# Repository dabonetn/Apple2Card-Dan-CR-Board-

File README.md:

This is my take on a surface mount version of the DAN II Card.

This version removes all the debug headers, and adds jumpers to the resistors for the Wiznet Header. (R27 & R28 on the original board)

ICSP port always provides power, and I don't recommend adding a header to this connector, but just use a male pinheader to program the unit.

This schematic allows cutting a jumper for 27256 or 27512 eprom chips programmed at the beginning of the chip, or leave it as is and program these chips at offset $4000.

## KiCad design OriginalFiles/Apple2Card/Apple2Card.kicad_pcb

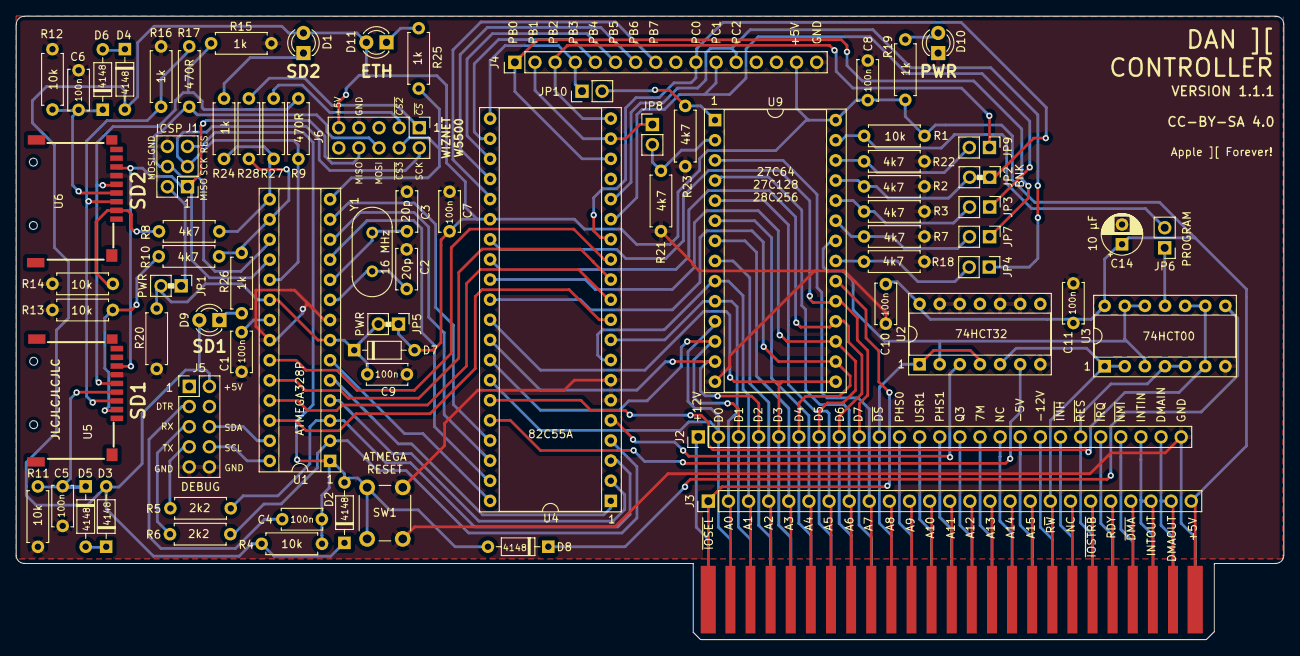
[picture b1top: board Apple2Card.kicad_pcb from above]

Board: 2 copper layers, 160.0 x 78.7 mm, 77 parts (0 on the bottom side), 116 nets.

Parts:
BUS1: Apple2Bus; Apple2Slot
C1, C4, C5, C6, C7, C8, C9, C10, C11: 100n; C_Disc_D5.0mm_W2.5mm_P5.00mm
C2, C3: 20p; C_Disc_D5.0mm_W2.5mm_P5.00mm
C14: 10 µF; CP_Radial_D5.0mm_P2.50mm
D1, D9, D10, D11: LED; LED_D3.0mm
D2, D3, D4, D5, D6, D7, D8: 4148; D_DO-35_SOD27_P7.62mm_Horizontal
J1: ICSP; PinHeader_2x03_P2.54mm_Vertical
J2, J3: Conn_01x25; PinHeader_1x25_P2.54mm_Vertical
J4: Conn_01x16; PinHeader_1x16_P2.54mm_Vertical
J5: SERCON; PinHeader_2x05_P2.54mm_Vertical
J6: WIZNET 5500; PinHeader_2x05_P2.54mm_Vertical
JP1, JP5: PWR; PinHeader_1x02_P2.54mm_Vertical
JP2: PG0; PinHeader_1x02_P2.54mm_Vertical
JP3: PG1; PinHeader_1x02_P2.54mm_Vertical
JP4, JP9: PG2; PinHeader_1x02_P2.54mm_Vertical
JP6: PROGRAM; PinHeader_1x02_P2.54mm_Vertical
JP7: PG3; PinHeader_1x02_P2.54mm_Vertical
JP8: PG4; PinHeader_1x02_P2.54mm_Vertical
JP10: PG9; PinHeader_1x02_P2.54mm_Vertical
R1, R4, R11, R12, R13, R14, R20: 10k; R_Axial_DIN0207_L6.3mm_D2.5mm_P7.62mm_Horizontal
R2, R3, R7, R8, R10, R18, R21, R22, R23: 4k7; R_Axial_DIN0207_L6.3mm_D2.5mm_P7.62mm_Horizontal
R5, R6: 2k2; R_Axial_DIN0207_L6.3mm_D2.5mm_P7.62mm_Horizontal
R9, R17, R27, R28: 470R; R_Axial_DIN0207_L6.3mm_D2.5mm_P7.62mm_Horizontal
R15, R16, R19, R24, R25, R26: 1k; R_Axial_DIN0207_L6.3mm_D2.5mm_P7.62mm_Horizontal
SW1: SW_Push; SW_PUSH_6mm
U1: ATmega328P-P; DIP-28_W7.62mm_Socket
U2: 74HCT32; DIP-14_W7.62mm_Socket
U3: 74HCT00; DIP-14_W7.62mm_Socket
U4: 82C55A; DIP-40_W15.24mm_Socket
U5: Slot1; GCT-MEM2055-00-190-01-A
U6: Slot2; GCT-MEM2055-00-190-01-A
U9: 28C256; DIP-28_W15.24mm_Socket
Y1: 16 MHz; Crystal_HC49-U_Vertical

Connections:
+5V: BUS1.25 (+5V), C7.1, C8.1, C10.1, C11.1, C14.1, D1.2 (A), D2.1 (K), D3.2 (A), D4.2 (A), D7.2 (A), D9.2 (A), D11.2 (A), J3.25, J4.15, J5.2, J6.9, JP5.1 (A), R1.1, R4.1, R19.1, U2.14 (VCC), U3.14 (VCC), U4.26 (VCC), U9.28 (VCC)
A0: BUS1.2 (A0), J3.2, U4.9 (A0), U9.10 (A0)
A1: BUS1.3 (A1), J3.3, U4.8 (A1), U9.9 (A1)
A2: BUS1.4 (A2), J3.4, U9.8 (A2)
A3: BUS1.5 (A3), J3.5, U9.7 (A3)
A4: BUS1.6 (A4), J3.6, U9.6 (A4)
A5: BUS1.7 (A5), J3.7, U9.5 (A5)
A6: BUS1.8 (A6), J3.8, U9.4 (A6)
A7: BUS1.9 (A7), J3.9, U9.3 (A7)
ACKA: U1.25 (PC2), U4.11 (PC6)
CS: R10.1, R26.2, R28.1, U1.16 (PB2)
CS2: R8.1, R24.2, R27.1, U1.15 (PB1)
CS3: J6.4, R25.2, U1.14 (PB0)
D0: BUS1.49 (D0), J2.2, U4.34 (D0), U9.11 (D0)
D1: BUS1.48 (D1), J2.3, U4.33 (D1), U9.12 (D1)
D2: BUS1.47 (D2), J2.4, U4.32 (D2), U9.13 (D2)
D3: BUS1.46 (D3), J2.5, U4.31 (D3), U9.15 (D3)
D4: BUS1.45 (D4), J2.6, U4.30 (D4), U9.16 (D4)
D5: BUS1.44 (D5), J2.7, U4.29 (D5), U9.17 (D5)
D6: BUS1.43 (D6), J2.8, U4.28 (D6), U9.18 (D6)
D7: BUS1.42 (D7), J2.9, U4.27 (D7), U9.19 (D7)
DS: BUS1.41 (~DEVICE_SELECT), J2.10, U2.1, U2.4
GND: BUS1.26 (GND), C1.2, C2.2, C3.2, C5.2, C6.2, C7.2, C8.2, C9.2, C10.2, C11.2, C14.2, D10.1 (K), J1.6, J2.25, J4.16, J5.9, J5.10, J6.7, R2.2, R3.2, R7.2, R11.1, R12.1, R13.2, R14.2, R15.2, R16.2, R18.2, R20.1, R21.2, R22.2, R23.2, SW1.2, U1.8 (GND), U1.22 (GND), U2.7 (GND), U2.9, U2.10, U2.12, U2.13, U3.7 (GND), U4.6 (~CS), U4.7 (GND), U5.6 (GND), U6.6 (GND), U9.14 (GND)
IBFA: U1.24 (PC1), U4.12 (PC5)
IOSEL: BUS1.1 (~IOSEL), J3.1, U9.20 (~CS)
MISO: J1.1, J6.8, U1.18 (PB4), U5.7 (DO), U6.7 (DO)
MOSI: J1.4, J6.6, R17.2, U1.17 (PB3)
unnamed: BUS1.10 (A8), J3.10
unnamed: BUS1.11 (A9), J3.11
unnamed: BUS1.12 (A10), J3.12
unnamed: BUS1.13 (A11), J3.13
unnamed: BUS1.14 (A12), J3.14
unnamed: BUS1.15 (A13), J3.15
unnamed: BUS1.16 (A14), J3.16
unnamed: BUS1.17 (A15), J3.17
unnamed: BUS1.19 (NC), J3.19
unnamed: BUS1.20 (~IO_STROBE), J3.20
unnamed: BUS1.21 (RDY), J3.21
unnamed: BUS1.22 (~DMA), J3.22
unnamed: BUS1.23 (INT_OUT), BUS1.28 (INT_IN), J2.23, J3.23
unnamed: BUS1.24 (DMA_OUT), BUS1.27 (DMA_IN), J2.24, J3.24
unnamed: BUS1.29 (~NMI), J2.22
unnamed: BUS1.30 (~IRQ), J2.21
unnamed: BUS1.32 (~INH), J2.19
unnamed: BUS1.33 (-12V), J2.18
unnamed: BUS1.34 (-5V), J2.17
unnamed: BUS1.35 (NC), J2.16
unnamed: BUS1.36 (7M), J2.15
unnamed: BUS1.37 (Q3), J2.14
unnamed: BUS1.38 (PHASE1), J2.13
unnamed: BUS1.39 (USER_1), J2.12
unnamed: BUS1.40 (PHASE0), J2.11
unnamed: BUS1.50 (+12V), J2.1
unnamed: C1.1, U1.21 (AREF)
unnamed: C2.1, U1.9 (XTAL1/PB6), Y1.2
unnamed: C3.1, U1.10 (XTAL2/PB7), Y1.1
unnamed: C4.1, J5.3
unnamed: C5.1, D5.1 (K), R11.2, U5.4 (VDD)
unnamed: C6.1, D6.1 (K), R12.2, U6.4 (VDD)
unnamed: C9.1, D7.1 (K), JP1.2 (B), JP5.2 (B), R20.2, U1.7 (VCC), U1.20 (AVCC)
unnamed: D1.1 (K), R24.1
unnamed: D3.1 (K), D5.2 (A)
unnamed: D4.1 (K), D6.2 (A)
unnamed: D8.1 (K), U3.8
unnamed: D9.1 (K), R26.1
unnamed: D10.2 (A), R19.2
unnamed: D11.1 (K), R25.1
unnamed: J1.2, JP1.1 (A)
unnamed: J4.5, U4.22 (PB4)
unnamed: J4.6, U4.23 (PB5)
unnamed: J4.7, U4.24 (PB6)
unnamed: J4.8, U4.25 (PB7)
unnamed: J5.5, R6.1
unnamed: J5.7, R5.1
unnamed: J6.1, R28.2
unnamed: J6.3, R27.2
unnamed: JP2.2 (B), R2.1, U9.25 (A8)
unnamed: JP3.2 (B), R3.1, U9.24 (A9)
unnamed: JP4.2 (B), R18.1, U9.21 (A10)
unnamed: JP6.1 (A), U3.11
unnamed: JP6.2 (B), R1.2, U9.27 (~WE)
unnamed: JP7.2 (B), R7.1, U9.23 (A11)
unnamed: JP8.2 (B), R21.1, U9.2 (A12)
unnamed: JP9.2 (B), R22.1, U9.26 (A13)
unnamed: JP10.2 (B), R23.1, U9.1 (A14)
unnamed: R10.2, R13.1, U5.2 (~CS)
unnamed: R8.2, R14.1, U6.2 (~CS)
unnamed: R9.2, R15.1, U5.5 (SCLK), U6.5 (SCLK)
unnamed: R16.1, R17.1, U5.3 (DI), U6.3 (DI)
unnamed: U2.2, U3.3, U3.12, U3.13, U9.22 (~OE)
unnamed: U2.3, U4.5 (~RD)
unnamed: U2.6, U4.36 (~WR)
unnamed: U3.6, U3.9, U3.10, U4.35 (RESET)
OBFA: U1.26 (PC3), U4.10 (PC7)
PB0: J4.1, JP7.1 (A), U4.18 (PB0)
PB1: J4.2, JP8.1 (A), U4.19 (PB1)
PB2: J4.3, JP9.1 (A), U4.20 (PB2)
PB3: J4.4, JP10.1 (A), U4.21 (PB3)
PC0: J4.10, JP2.1 (A), U4.14 (PC0)
PC1: J4.11, JP3.1 (A), U4.15 (PC1)
PC2: J4.12, JP4.1 (A), U4.16 (PC2)
PC4: J5.6, U1.27 (PC4)
PC5: J5.8, U1.28 (PC5)
PD0: R6.2, U1.2 (PD0), U4.4 (PA0)
PD1: R5.2, U1.3 (PD1), U4.3 (PA1)
PD2: U1.4 (PD2), U4.2 (PA2)
PD3: U1.5 (PD3), U4.1 (PA3)
PD4: U1.6 (PD4), U4.40 (PA4)
PD5: U1.11 (PD5), U4.39 (PA5)
PD6: U1.12 (PD6), U4.38 (PA6)
PD7: U1.13 (PD7), U4.37 (PA7)
RES: BUS1.31 (~RES), J2.20, U3.4, U3.5
RESET: C4.2, D2.2 (A), D8.2 (A), J1.5, R4.2, SW1.1, U1.1 (~RESET/PC6)
RW: BUS1.18 (R/~W), J3.18, U2.5, U3.1, U3.2
SCK: J1.3, J6.2, R9.1, U1.19 (PB5)
STBA: U1.23 (PC0), U4.13 (PC4)

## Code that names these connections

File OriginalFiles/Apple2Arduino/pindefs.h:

/* pindefs.h */
/* by Daniel L. Marks */

/*
 * Copyright (c) 2022 Daniel Marks

This software is provided 'as-is', without any express or implied
warranty. In no event will the authors be held liable for any damages
arising from the use of this software.

Permission is granted to anyone to use this software for any purpose,
including commercial applications, and to alter it and redistribute it
freely, subject to the following restrictions:

1. The origin of this software must not be misrepresented; you must not
   claim that you wrote the original software. If you use this software
   in a product, an acknowledgment in the product documentation would be
   appreciated but is not required.
2. Altered source versions must be plainly marked as such, and must not be
   misrepresented as being the original software.
3. This notice may not be removed or altered from any source distribution.
 */

#ifndef _PINDEFS_H
#define _PINDEFS_H

#define DAN_328P  3
#define DAN_644P  4

#if defined(__AVR_ATmega328P__)
#define CS     2    // PB2
#define CS2    1     // PB1
#define CS3    0     // PB0
#define D_CS3  8     // PB0 in Arduino Digital pin

#define MOSI   3    // PB3
#define MISO   4    // PB4
#define SCK    5    // PB5

#define STBA   0  // PC0
#define IBFA   1  // PC1
#define ACKA   2  // PC2
#define OBFA   3  // PC3
#define DAN_CARD     DAN_328P
#elif defined(__AVR_ATmega644P__)
#define CS     2     // PB2
#define CS2    1     // PB1
#define CS3    0     // PB0
#define D_CS3  8     // PB0 in Arduino Digital pin

#define MOSI   5    // PB5
#define MISO   6    // PB6
#define SCK    7    // PB7
#define SLAVE_S 4   // PB4 SS PIN *needs* to be configured as it's floating!

#define STBA   6  // PC6
#define IBFA   7  // PC7
#define ACKA   2  // PC2
#define OBFA   3  // PC3
#define DAN_CARD     DAN_644P
#else
#error Invalid platform for pindef.h!
#endif

#define SOFTWARE_SERIAL
#define SOFTWARE_SERIAL_RX A4
#define SOFTWARE_SERIAL_TX A5

#define CS_ALL			(_BV(CS)|_BV(CS2)|_BV(CS3))
/* Make sure we never use PORTB = XXX as it nukes settings for the SS pin */
#define DISABLE_CS() do { PORTB |= CS_ALL; DDRB |= CS_ALL; } while (0)
#define DISABLE_RXTX_PINS() UCSR0B &= ~(_BV(RXEN0)|_BV(TXEN0)|_BV(RXCIE0)|_BV(UDRIE0))
#define ENABLE_RXTX_PINS() UCSR0B |= (_BV(RXEN0)|_BV(TXEN0)|_BV(RXCIE0)|_BV(UDRIE0))
#define WAIT_TX() while ((UCSR0A & _BV(TXC0) == 0)

#define DATAPORT_MODE_TRANS() DDRD = 0xFF
#define DATAPORT_MODE_RECEIVE() do { PORTD = 0x00; DDRD = 0x00; } while (0)

#define READ_DATAPORT() (PIND)
#define WRITE_DATAPORT(x) do { uint8_t temp = (x); PORTD=temp; PORTD=temp; } while (0)

#define READ_OBFA() (PINC & _BV(OBFA))
#define READ_IBFA() (PINC & _BV(IBFA))
#define ACK_LOW_SINGLE() PORTC &= ~_BV(ACKA)
#define ACK_HIGH_SINGLE() PORTC |= _BV(ACKA)
#define STB_LOW_SINGLE() PORTC &= ~_BV(STBA)
#define STB_HIGH_SINGLE() PORTC |= _BV(STBA)

/* Needed to slow down data send for 82C55 */

// Ack has to be 200ns -- 16mhz AVR cycle is ~63
// ACK to data available is 175ns, so 3 cycles of ACK low should be enough
#define ACK_LOW() do { \
                     ACK_LOW_SINGLE(); ACK_LOW_SINGLE(); ACK_LOW_SINGLE(); \
                     ACK_LOW_SINGLE(); ACK_LOW_SINGLE(); \
                  } while (0)
// the read operation should be one cycle, so we reach 200ns and we can release ACK immediately
#define ACK_HIGH() do { ACK_HIGH_SINGLE();  } while (0)
// STB to IBS is 150ns, that's 3 AVR cycles, however, we don't /need/ to wait, we could just read IBS
#define STB_LOW() do { \
                        STB_LOW_SINGLE(); STB_LOW_SINGLE(); STB_LOW_SINGLE(); \
                        STB_LOW_SINGLE(); STB_LOW_SINGLE();\
                  } while (0)
#define STB_HIGH() do { STB_HIGH_SINGLE(); } while (0)

#define INITIALIZE_CONTROL_PORT() do { \
  PORTC |= (_BV(STBA) | _BV(IBFA) | _BV(ACKA) | _BV(OBFA)); \
  DDRC |= (_BV(STBA) | _BV(ACKA)); \
  DDRC &= ~(_BV(IBFA) | _BV(OBFA)); \
  PORTC |= (_BV(STBA) | _BV(IBFA) | _BV(ACKA) | _BV(OBFA)); \
} while (0)

#endif /* _PINDEFS_H */

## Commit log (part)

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2023-03-18 Improved boot menu. Added title and footer bar. Added ":" separators. Added option to keep existing card selection by pressing RETURN. Wipe screen before reboot. Swapped RETURN and SPACE keys in ROM 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
2023-03-24 Improved SD-card compatibility (and performance)
    1. Compatibility fix for some SD cards
    After a power-down an SD card will always immediately respond to CMD0
    ("GO IDLE" command) with "1" ("in idle state"). However, since this controller
    hardware does not support physical power-down/reset, a card which was already
    initialized may also respond to CMD0 with "0" (=not idle (yet)), if it's still
    busy. In this case we need to briefly wait and poll the state again, until
2023-04-02 Improved bootpg build infrastructure Moved boot program to separate directory. Added option to build several boot programs. Readded original bootpg v2 by DL Marks as an option. Moved bootpg binary da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
2023-04-08 Minor command updates/extensions. Adapted do_get_volume command to return the EEPROM volume configuration, not the current (temporary) volume selection, which is what the config utility really wants 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
2023-04-08 Makefiles + project structure Moved volumes and utilities to separate directories. Build all binaries in "bin/" subdirectories to keep the source directories tidy. Added AppleCommander utility (java)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
2023-04-08 Added sram loader utility. To use an SRAM (32KB, 62256) instead of a ROM/EEPROM for debugging.
2023-04-20 Disable FatFs codepage support to save RAM. We don't care about filenames with non-ASCII characters. We only ever use known fixed and plain ASCII names anyway (BLKDEVXX.PO).
2023-04-20 Moved configuration to separate header file.
2023-04-20 Added optional memory overflow detection to detect when stack runs into the heap area.
2023-04-21 Added FTP server to Arduino. Apple II access is suspended while any FTP client is connected. FTP server is shut down when Apple II takes control of the Eth port (IP65 lib).
2023-04-22 Minor optimizations, freeing up more (flash) memory.
2023-04-22 Proper fix for MMC vs WIZnet SPI issues. Now takes proper care when the SPI bus is still blocked, before accessing the WIZnet SPI device.
2023-04-30 Added firmware update utility for the DAN][ controller (Arduino firmware). Also added hex file with the customized Arduino bootloader (see https://github.com/ThorstenBr/MiniCoreDAN2Controller on how 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
2023-05-04 Renamed "firmware" and "flash" to "eprom" to avoid confusion with the Arduino flash. Slightly restructured the utilities folder.
2023-05-04 Also added ip65.po since this format can directly be run as a volume on the DAN][card.
2023-05-04 More documentation updates.
2023-05-05 Add alternate 3D Ethernet bracket. Minor fix to build order of Arduino vs boot programs.
2023-05-08 Integrated FTP/IP configuration into the boot menu. The separate utility is now obsolete (still working but no longer required).
2023-05-13 Also moved "allvols" utility to separate folder below "utilities".
2023-05-13 Dropped binary images of IP config disks. The utility is no longer needed, since this is now integrated into the boot menu. Also, any built binary images (disks etc) should go to "releases", and not 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
2023-05-13 Add FTP support for Raw Block Mode. SD Cards using Raw Block Mode are now also accessible via FTP. For safety reasons the SD card format is now auto-detected, rather than manually configured (using "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
2023-05-13 Automated release build. Build a ZIP file with all binaries/hex files for a GitHub release
2023-06-05 Minor updates/corrections to documenation. Quick access keys and ADTPro support.
2023-07-02 Minor tweaks & corrections Fixed build dependency with cpp files. Keep FTP/IP feature disabled on new cards (needs to be enabled manually). Enable builds without bootpg (to save space for debugging).
2023-07-02 Fixed minor makefile issues. Proper clean-up rules.
2023-07-02 Added a kludge to fix a warmstart issue with the custom bootloader (new custom bootloader + Arduino firmware). This fixes a deadlock when ProDOS accesses a disk immediately after a warmstart (after C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
2023-07-02 Renamed the utility disk, revised Makefiles.
2023-07-04 Minor improvements to utilities.
2023-07-04 New firmware with more flexible drive mapping. Drive 1+2 can now be mapped to any volume on any SD card. Limitations between RAW and FAT disks are completely removed - even the ALLVOLS mapping now wo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
2023-07-04 Allow FTP to write slightly oversized files of 65536x512 bytes. ProDOS only support up to 65535 blocks (of 512 byte). However, some raw images "on the internet" actually still have 65536 blocks. So, 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
2023-07-08 Adapted description of volume selection to latest firmware.
2023-07-30 Just improved label naming.
2023-07-30 v3.1.0: New/improved DOS/FAT file naming scheme Now uses "VOLxx...PO" filenames for FAT, and only considers the first 5 bytes (and the file extension).
    So you can now use longer filenames on the SD cards, to keep files organized, e.g.:
    VOL00_TOTALREPLAY.PO
    VOL01_InstantReplay.PO
    ...
    VOL0F_FooBar.PO
    etc
2023-07-30 Minor typo.
2023-08-05 Removed 512byte padding from boot program to save flash memory. A run-time check is much cheaper (smaller) than padding the entire data block.
2023-08-05 Removed obsolete config option. No longer had any effect. Option was replaced by the more flexible configuration menu.
2023-08-09 Bugfix for FAT support: Properly close the file handle before switching to another file on the same disk. This sometimes caused FAT files to be not properly opened (not being accessible).
2023-08-09 Minor fix to clean-up rule. Make sure _all_ generated content is removed when calling "make clean".
2023-08-09 x44: Updated the schematics .pdf
    'Printed' the new A3 version.
    Also added a Readme with a warning, as nothing has been tested yet.
2023-08-09 644: Added support for the DANII bootloader version
    Made from the repo at
    https://github.com/ThorstenBr/MiniCoreDAN2Controller.git
    Also, added bin-* to the gitignore
2023-08-09 Minor updates to PCB & schematics: - Realigned some components (LEDs etc). - Added some clearance to the slot connector (now allows production with "chamfered edges"). - Show component values on the 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
2023-08-25 Minor documentation fixes.
2023-08-25 Removed duplicated call (saves 10bytes of memory - every little counts...)
2023-09-03 Added optional file for local environment setup. localsettings.mk can be used (locally) to set up a path for arduino-cli, or to configure the DANII controller's IP address and volume file for local t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
2023-09-03 Fixed Makefile abort-on-error issues. "make build" no longer aborted with an error (caused by the "||" to print an error message for installation errors). Separated the installation check into a sepa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
2023-09-03 Rebuild for version 3.2.0. Intermediate release for improved Apple /// support.
2023-09-03 mmc: Use pin definitions instead of hard coded values
    * Removed <Arduino.h>, turns out it's not needed
    * Converted all macros to use names found in pindefs.h
    * Changed power_on to use the macros, AND make sure we don't nuke bits
    of PORTB we aren't suposed to touch
2023-09-03 w5500: Use pindefs names
    Same in this file, just remove the hard constants to use names, and also
    make sure we don't nuke the DDRB pins.
2023-09-03 main: 644: Make sure PORTB4 is configured!
    Make sure the SS pin is configured, otherwise SPI crashes during
    transfer
2023-09-03 644: Updated bootloader
    Nothing terribly functional in there, just use of the new pindefs macros
2023-09-03 Bump revision (in development).
2023-09-08 Customized the Ethernet library. Added feature switches to disable DNS+DHCP and legacy support for W5100/W5200 modules. This saves a ton of memory - freed up more than 4KB flash and >100bytes of RAM.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
2023-09-11 Trigger a PHY reset when initializing the Ethernet support. Since we don't have the RESET line connected to the Wiznet, triggering a full PHY reset is a good idea. It fixes occasional hickups with th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
2023-09-11 Added option to configure FTP user/password For now, this can only be configured at compile time, hence is not a standard feature. Will be improved later.
2023-09-11 Fixed makefile issue with missing "bin" directories.
2023-09-13 Added a firmware version command. Command returns a standard 512 byte block (usable by ROM routine), containing the firmware version, hardware type and feature flags.
2023-09-13 Adapted fwupdate makefile: - makefile now accepts a ATMEGA_TYPE=... (328P/644P) parameter to select target. - output is written to bin-328p/bin-644p directories. - set a define "ATMEGA328P" or "ATMEG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
2023-09-13 fwupdate: Compile a 644 and a 328 fwupdate! Revised patch by Michel Pollet <buserror@gmail.com> for ATMEGA644P support. - Adapted to switch between ATMEGA328 and ATMEGA644 page size. - Consider actua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
2023-09-13 Updated 644P bootloader to support the new "STK_DANII_TYPE" parameter, which reports "type 4" for ATMEGA644P (while ATMEGA328P reports "3"). (ATMEGA328P does not need to be updated, since all existin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
2023-09-13 Added hardware type check to fw update utility. Show board type (ATMEGA328P vs 644P). Prevent update when type mismatches. Add firmware updater for ATmega328P and 644P (if present).
2023-09-16 Removed duplicated/incorrect Makefile rule.
2023-09-20 Added ethernet bracket for Apple ///.
2023-09-23 Changed FTP data port for passive FTP. According to the standard a port between 1024-65535 is to be used for data connections of passive FTP. Port 20 is the standard for active FTP. We're always usin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
2023-09-23 Minor: fix assembler warning about unused local label.
2023-09-25 Improved 3D enclosure for Apple IIe Ethernet bracket. Fits into the Apple IIe's DB19 opening next to slot 7.
2023-09-30 Update README.md
    Removed the outdated section on "wide block mode". With the latest firmware, this is no longer a "mode" of the SD cards. It's an independent feature which works with any SD cards in any mode (FAT or 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
2023-10-03 Minor tweak to silkscreen: indicator where fixed jumpers should be soldered.
2023-10-06 Added APPLE /// SOS volume template. Dropped DOS3.3 template.
2023-10-07 Refactored firmware update utility to support Apple /// SOS and Apple II ProDOS. - Revised Apple III firmware update to be a native SOS executable (rather than an Apple II DOS executable to be run in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
2023-10-07 Uff. Fixed the mysterious issue with Apple III resets. Adds extra synchronisation to workaround an Apple III hardware bug, where the NMI was already executed while IO was still reset and unable to re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
2023-10-07 Set new version: 3.3.3 (with updates for Apple III...)
2023-10-19 Trigger immediate FTP re-initialization when IP configuration changed.
2023-10-19 Also boost the FTP server to show up to 128 volumes.
2023-10-19 Fixed issue with menu when aborting the configuration. When aborting with ESCAPE, do not highlight volumes when these previously selected volumes are located on a different page.
2023-10-19 Do not show unused volumes on RAW disks when listing FTP directory contents.
2023-10-25 Provide better error message for active FTP connection attempts. Handle and reply to the "PORT" command, which initiates an active FTP session (which we do not support). Some minor clean-up.
2023-11-06 Updated hex file and build log for v3.4.0.
2023-11-06 Updated README for new "128 volumes per SD card" support.
2023-11-25 Fixed sporadic issue with menu showing mouse text instead of a flashing selection bar after a warm start. The soft switches in the Apple IIe IOU only receive a hardware reset at power-on. Run-time re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
2023-11-29 Added tiny bootpg stub for Apple ///. The Apple /// bootpg needs to be installed on the SD card, to save flash memory - and since most users with an Apple II don't need it. However, if the bootpg for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
2023-12-05 Added brief description and links for Apple III support which wasn't even mentioned in this README before.
2024-01-17 Added interactive BOM.

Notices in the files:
OriginalFiles/Apple2Card/Apple2Card.kicad_pcb:
CC-BY-SA 4.0
